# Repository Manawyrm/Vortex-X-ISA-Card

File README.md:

# Vortex-X-ISA-Card

Adapter for connecting a VortexDX computer to a 16-bit ISA backplane.  
Power can be supplied from the backplane. IRQs are supported, **DMA is NOT supported**.

## Status

RevA is fully functional and works well.

## Attribution

[sur5r](https://github.com/sur5r) - based on rough layout from [PC104-ISA-Card](https://github.com/Manawyrm/PC104-ISA-Card)

[Manawyrm](https://github.com/Manawyrm) - Schematic, PCB layout/routing

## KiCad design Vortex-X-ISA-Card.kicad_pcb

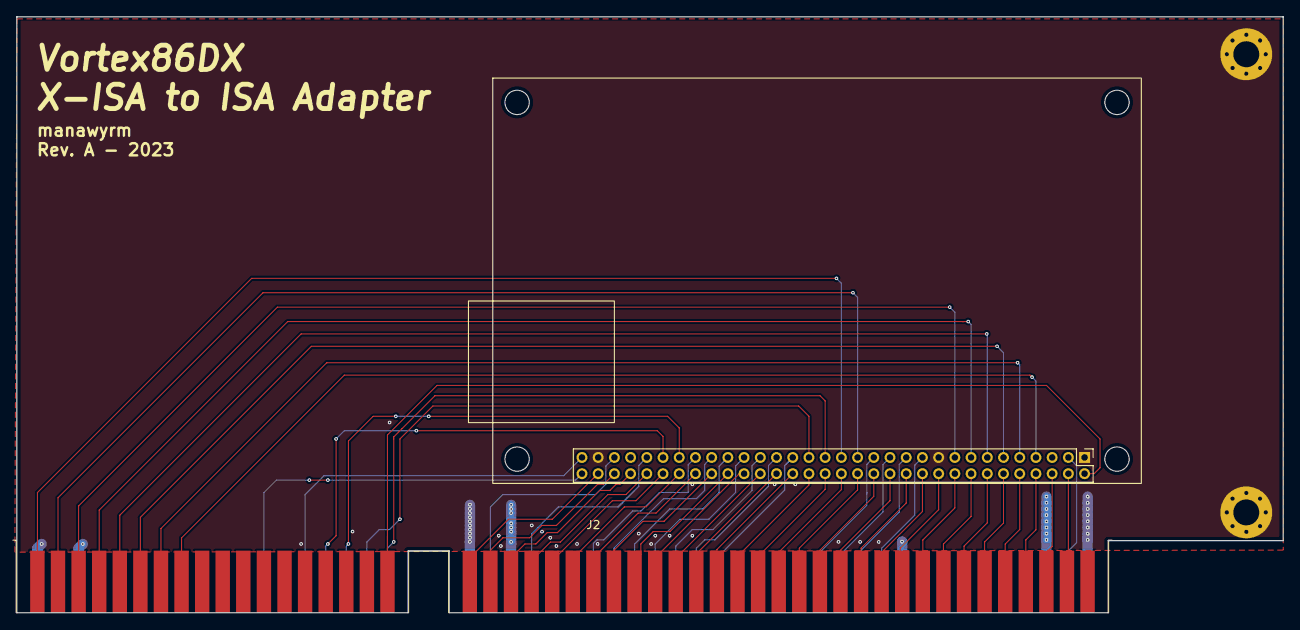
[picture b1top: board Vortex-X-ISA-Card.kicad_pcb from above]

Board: 4 copper layers, 156.2 x 73.5 mm, 4 parts (0 on the bottom side), 61 nets.

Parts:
H1, H2: MountingHole_3.2mm_M3_Pad_Via
J2: Bus_ISA_16bit; BUS_AT
U1: VDX-6317

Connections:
+5V: J2.3 (+5V), J2.29 (+5V), J2.78 (+5V), U1.5 (VCC), U1.57 (VCC)
/AEN: J2.42 (AEN), U1.22 (AEN)
/ALE/BALE: J2.28 (ALE), U1.55 (BALE)
/BA0/SA0: J2.62 (BA00), U1.62 (SA0)
/BA1/SA1: J2.61 (BA01), U1.60 (SA1)
/BA2/SA2: J2.60 (BA02), U1.58 (SA2)
/BA3/SA3: J2.59 (BA03), U1.56 (SA3)
/BA4/SA4: J2.58 (BA04), U1.54 (SA4)
/BA5/SA5: J2.57 (BA05), U1.52 (SA5)
/BA6/SA6: J2.56 (BA06), U1.50 (SA6)
/BA7/SA7: J2.55 (BA07), U1.48 (SA7)
/BA8/SA8: J2.54 (BA08), U1.46 (SA8)
/BA9/SA9: J2.53 (BA09), U1.44 (SA9)
/BA10/SA10: J2.52 (BA10), U1.42 (SA10)
/BA11/SA11: J2.51 (BA11), U1.40 (SA11)
/BA12/SA12: J2.50 (BA12), U1.38 (SA12)
/BA13/SA13: J2.49 (BA13), U1.36 (SA13)
/BA14/SA14: J2.48 (BA14), U1.34 (SA14)
/BA15/SA15: J2.47 (BA15), U1.32 (SA15)
/BA16/SA16: J2.46 (BA16), U1.30 (SA16)
/BA17/SA17: J2.45 (BA17), U1.28 (SA17)
/BA18/SA18: J2.44 (BA18), U1.26 (SA18)
/BA19/SA19: J2.43 (BA19), U1.24 (SA19)
/CLK/BCLK: J2.20 (CLK), U1.39 (SYSCLK)
/D8/SD8: J2.91 (D8), U1.7 (SD8)
/D9/SD9: J2.92 (D9), U1.9 (SD9)
/D10/SD10: J2.93 (D10), U1.11 (SD10)
/D11/SD11: J2.94 (D11), U1.13 (SD11)
/D12/SD12: J2.95 (D12), U1.15 (SD12)
/D13/SD13: J2.96 (D13), U1.17 (SD13)
/D14/SD14: J2.97 (D14), U1.29 (SD14)
/D15/SD15: J2.98 (D15), U1.31 (SD15)
/DB0/SD0: J2.40 (DB0), U1.18 (SD0)
/DB1/SD1: J2.39 (DB1), U1.16 (SD1)
/DB2/SD2: J2.38 (DB2), U1.14 (SD2)
/DB3/SD3: J2.37 (DB3), U1.12 (SD3)
/DB4/SD4: J2.36 (DB4), U1.10 (SD4)
/DB5/SD5: J2.35 (DB5), U1.8 (SD5)
/DB6/SD6: J2.34 (DB6), U1.6 (SD6)
/DB7/SD7: J2.33 (DB7), U1.4 (SD7)
/IO_READY/IOCHRDY: J2.41 (IO_READY), U1.20 (IOCHRDY)
/IRQ3: J2.25 (IRQ3), U1.49 (IRQ3)
/IRQ4: J2.24 (IRQ4), U1.47 (IRQ4)
/IRQ5: J2.23 (IRQ5), U1.45 (IRQ5)
/IRQ6: J2.22 (IRQ6), U1.43 (IRQ6)
/IRQ7: J2.21 (IRQ7), U1.41 (IRQ7)
/IRQ10: J2.65 (IRQ10), U1.51 (IRQ10)
/IRQ11: J2.66 (IRQ11), U1.53 (IRQ11)
/IRQ12: J2.67 (IRQ12), U1.63 (IRQ12)
/IRQ14: J2.69 (IRQ14), U1.64 (IRQ14)
/OSC: J2.30 (OSC), U1.59 (OSC)
/RESET: J2.2 (RESET), U1.3 (RSTDRV)
/SBHE/~{SBHE: J2.81 (SBHE), U1.2 (SBHE)
/~{IOCS16: J2.64 (~IOCS16), U1.35 (IOCS16)
/~IOR: J2.14 (~IOR), U1.27 (IOR)
/~IOW: J2.13 (~IOW), U1.25 (IOW)
/~{MEMCS16: J2.63 (~MEMCS16), U1.33 (MEMCS16)
/~{REFRESH: J2.19 (~REFRESH), U1.37 (REFRESH)
/~SMEMR: J2.12 (~SMEMR), U1.23 (SMEMR)
/~SMEMW: J2.11 (~SMEMW), U1.21 (SMEMW)
GND: H1.1, H2.1, J2.1 (GND), J2.10 (GND), J2.31 (GND), J2.80 (GND), U1.1 (GND), U1.19 (GND), U1.61 (GND)

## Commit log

2023-04-11 Implement VortexDX adapter
2023-04-17 Add README
